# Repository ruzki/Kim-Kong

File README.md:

# Kim Kong
Daughterboard based on STM32F407VGT6 for the Speeduino ECU Project <br />
License <br />

<br />
This is a KiCad project of an Daughterboard to fit the kdFi by k-data.org (all rights reserved)  Motherboard Footprint.
Use most recent KiCad Nighty Build Version to open this project. 

This is not an k-data.org prouduct nor is it licencsed by k-data.org. 
You may contact k-data.org before using this Board on original k-data.org hardware and ask for permission.

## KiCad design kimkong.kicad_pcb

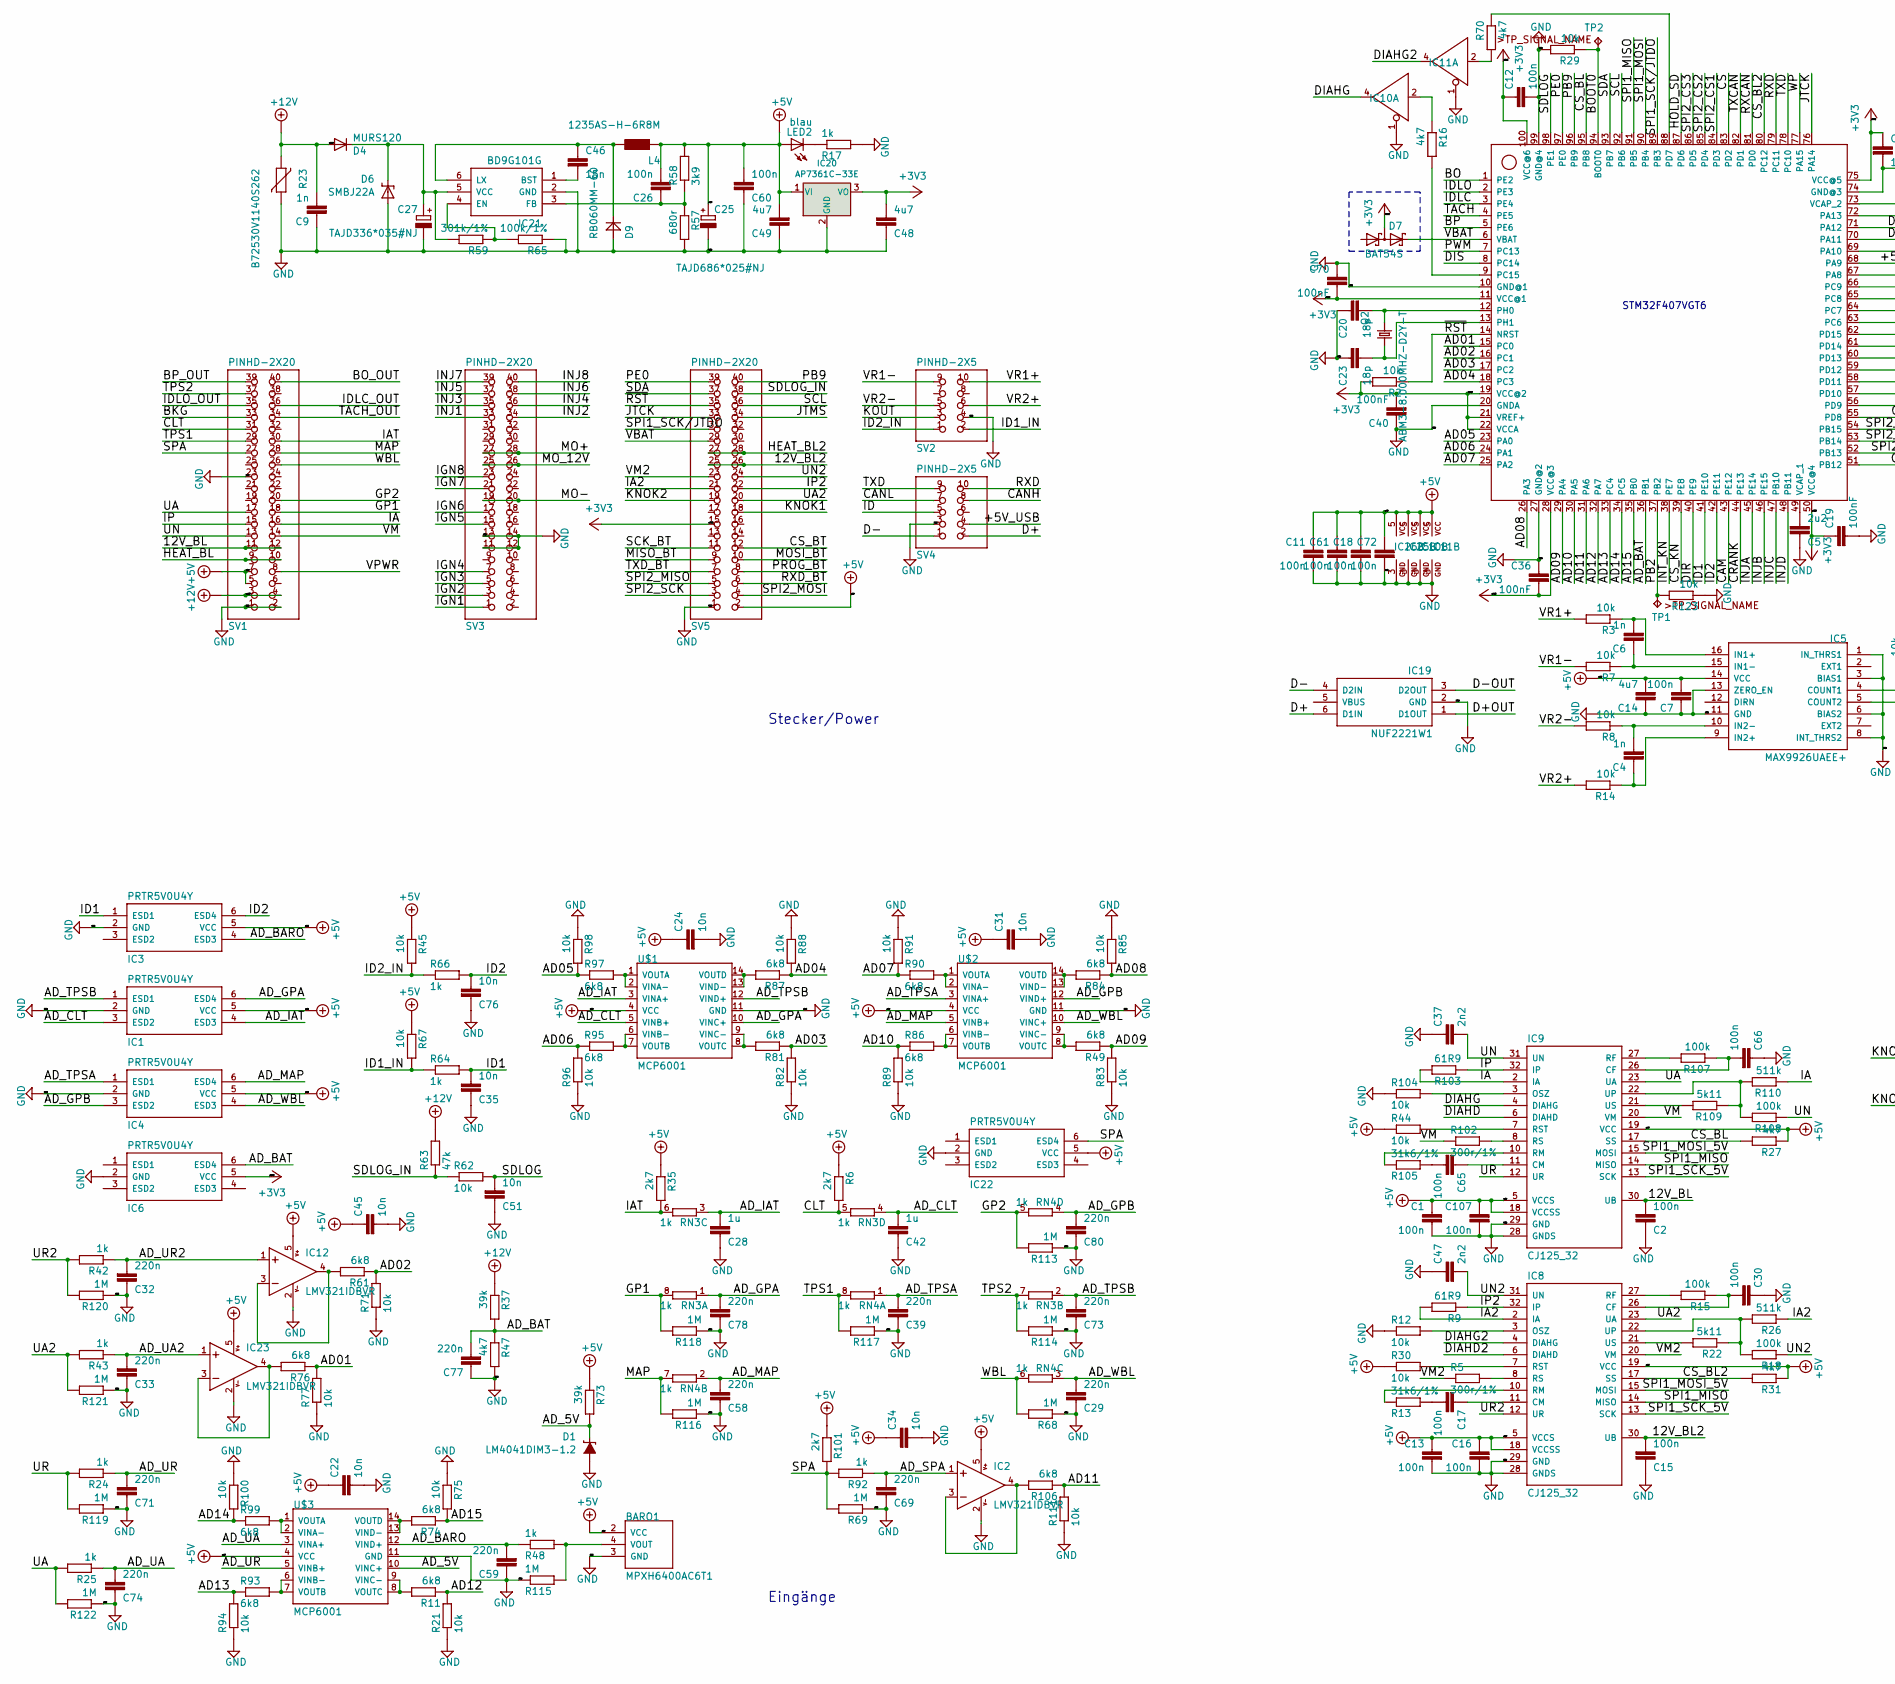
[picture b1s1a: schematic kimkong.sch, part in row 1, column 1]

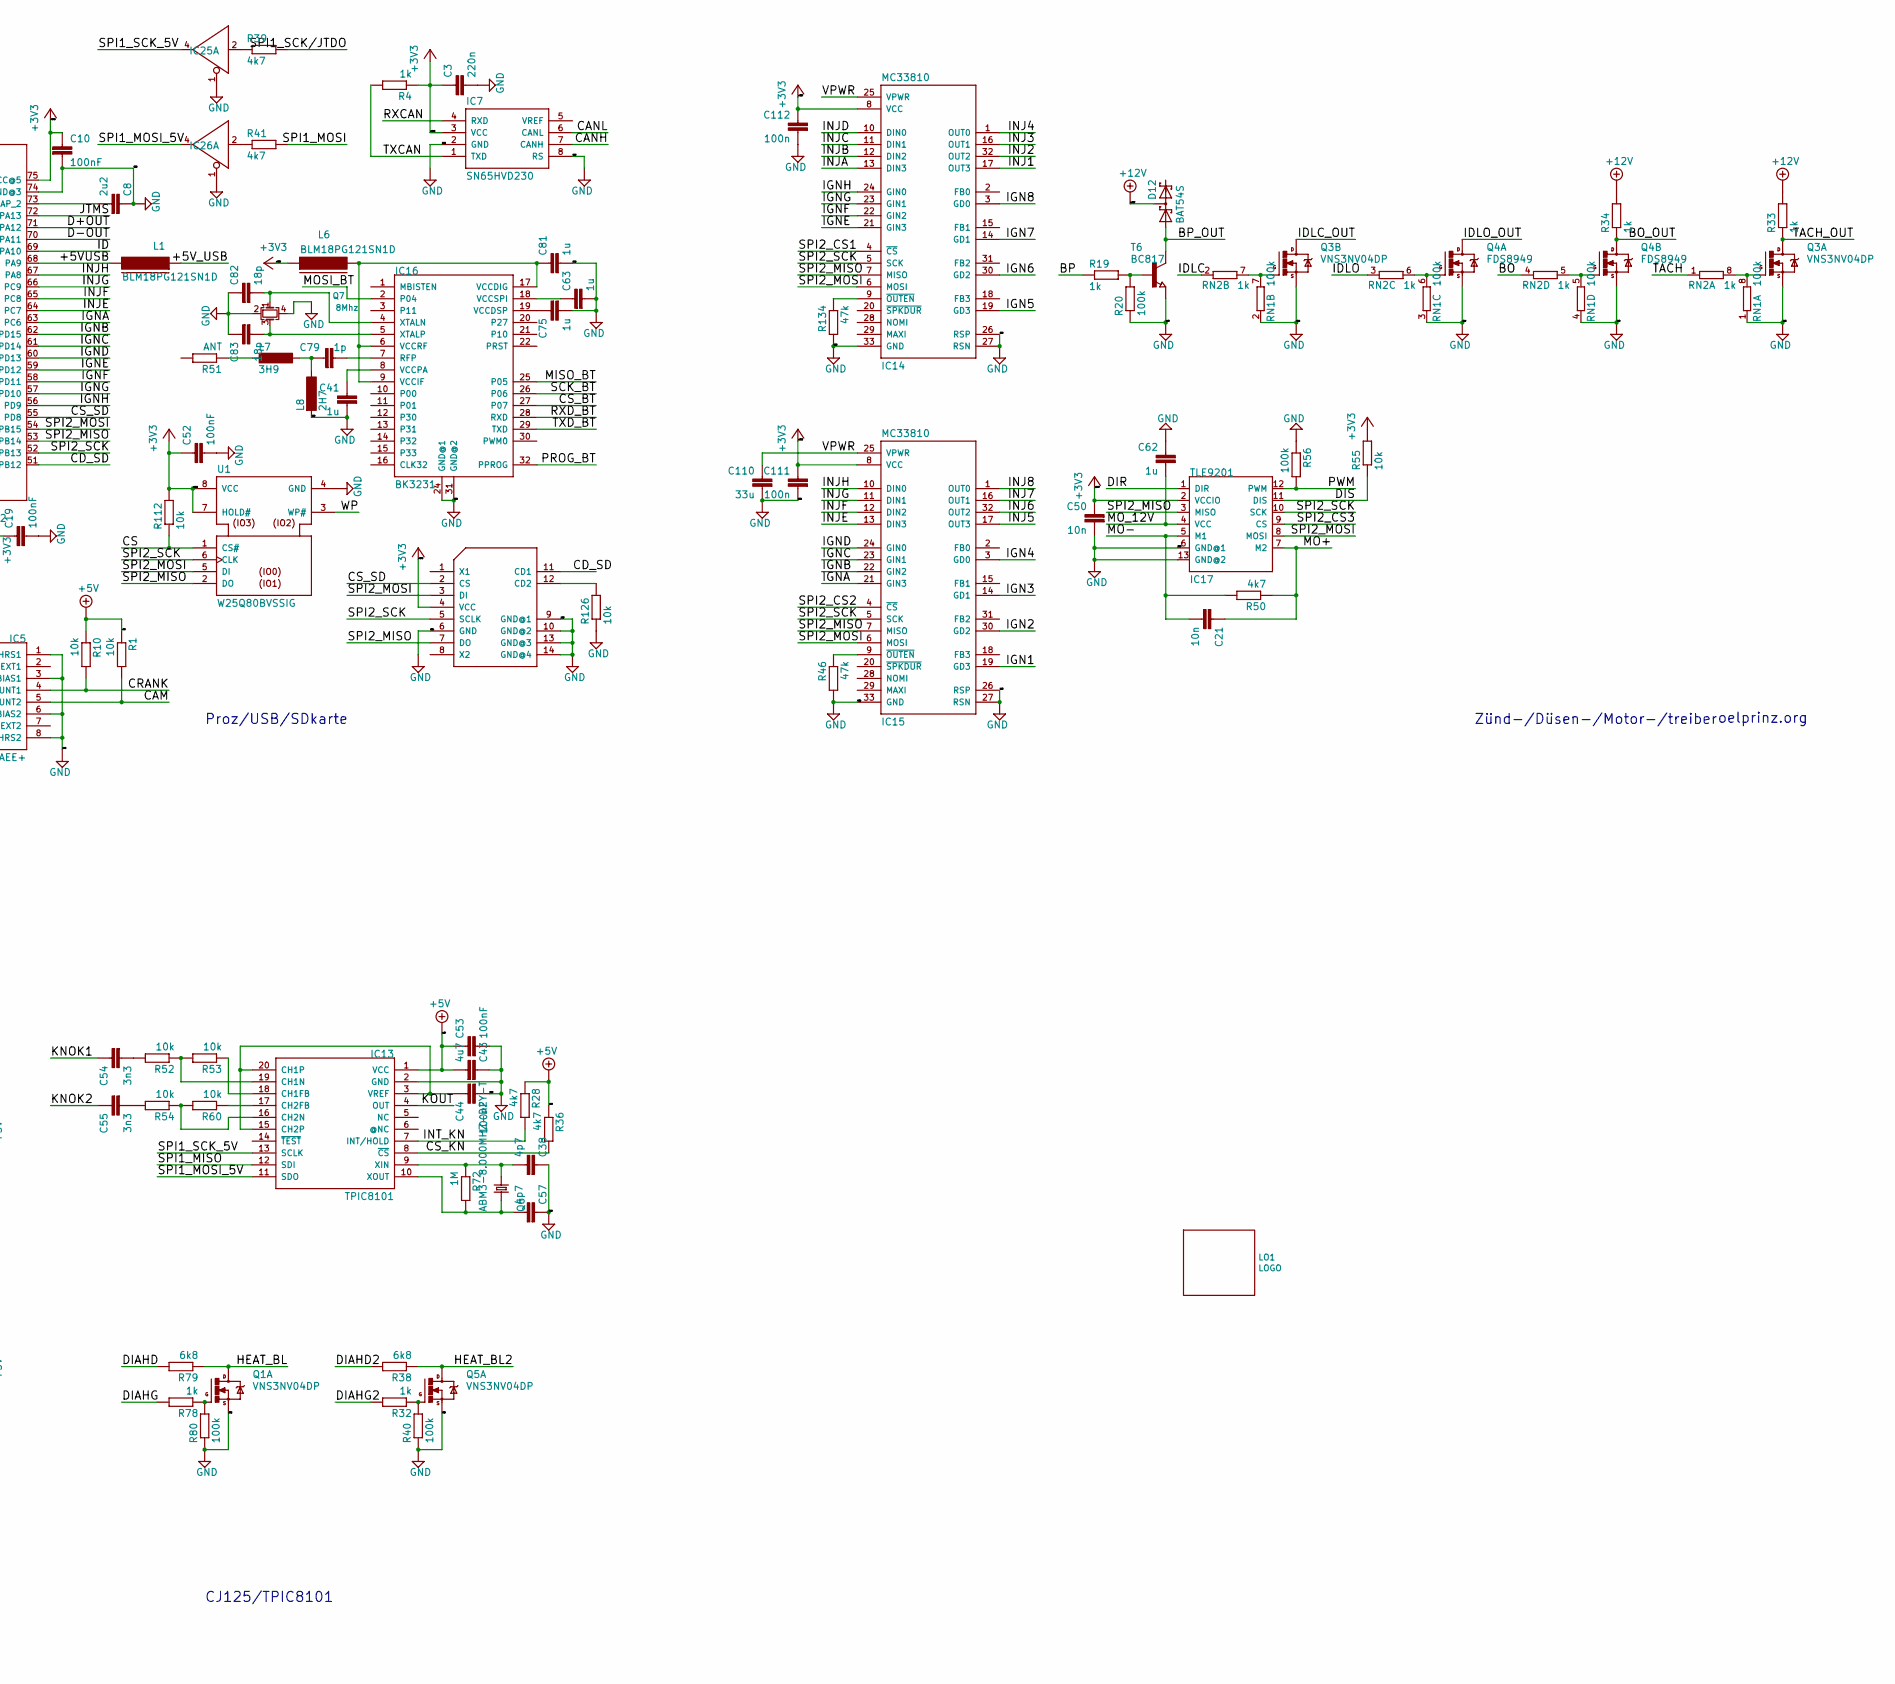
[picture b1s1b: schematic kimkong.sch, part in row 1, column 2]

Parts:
BARO1: MPXH6400AC6T1; Case1317
C1, C2, C7, C11, C12, C13, C15, C16, C17, C18, C26, C30, C60, C61, C65, C66, C72, C107, C111, C112: 100n; C0603
C3, C29, C32, C33, C39, C58, C59, C69, C71, C73, C74, C77, C78, C80: 220n; C0603
C4, C6: 1n; C0603
C5, C8: 2u2; C0603
C9: 1n; C0805
C10, C19, C36, C40, C44, C52, C53, C70: 100nF; C0603
C14, C48, C49: 4u7; C0603
C20, C23, C82, C83: 18p; C0603
C21: 10n; C1206
C22, C24, C31, C34, C35, C45, C50, C51, C76: 10n; C0603
C25: TAJD686*025#NJ; SMC_D
C27: TAJD336*035#NJ; SMC_D
C28, C41, C42, C62, C63, C75, C81: 1u; C0603
C37, C47: 2n2; C0603
C38, C57: 4p7; C0603
C43: 4u7; C0805
C46: 15n; C0603
C54, C55: 3n3; C0603
C79: 1p; C0603
C110: 33u; C1206
D1: LM4041DIM3-1.2; DBZ_R-PDSO-G3
D4: MURS120
D6: SMBJ22A; SMBJ
D7, D12: BAT54S; SOT23
D9: RB060MM-60
IC1, IC3, IC4, IC6, IC22: PRTR5V0U4Y; SOT363_PHILIPS
IC2, IC12, IC23: LMV321IDBVR; SC70-5L
IC5: MAX9926UAEE+; QSOP16
IC7: SN65HVD230; SO8
IC8, IC9: CJ125_32; TQFP32-08
IC10, IC11, IC25, IC26: 741G125DCK; SC70-5
IC13: TPIC8101; SO-20LD
IC14, IC15: MC33810
IC16: BK3231; QFN-32
IC17: TLE9201
IC18: STM32F407VGT6; LQFP100
IC19: NUF2221W1; SOT363_PHILIPS
IC20: AP7361C-33E; SOT-89-5_Housing
IC21: BD9G101G; SSOT6
L1, L6: BLM18PG121SN1D; FB805
L4: 1235AS-H-6R8M
L7: 3H9; L2012C
L8: 2H7; L2012C
LED2: blau; SML0805
LO1: LOGO; KimKong_40x50
Q1, Q3, Q5: VNS3NV04DP; M08A
Q2, Q6: ABM3-8.000MHZ-D2Y-T; ABM3
Q4: FDS8949; M08A
Q7: 8Mhz; ABM11
R1, R2, R10, R12, R21, R29, R30, R44, R45, R52, R53, R54, R55, R60, R62, R67, R71, R75, R77, R82, R83, R85, R88, R89, R91, R94, R96, R98, R100, R104, R111, R112, R123, R126: 10k; R0603
R3, R7, R8, R14: 10k; R1206
R4, R17, R19, R24, R25, R32, R33, R34, R42, R43, R48, R64, R66, R78, R92: 1k; R0603
R5, R102: 300r/1%; R0603
R6, R35, R101: 2k7; R0603
R9, R103: 61R9; R0603
R11, R38, R49, R61, R74, R76, R79, R81, R84, R86, R87, R90, R93, R95, R97, R99, R106: 6k8; R0603
R13, R105: 31k6/1%; R0603
R15, R18, R20, R40, R56, R80, R107, R108: 100k; R0603
R16, R27, R28, R31, R36, R39, R41, R47, R70: 4k7; R0603
R22, R109: 5k11; R0603
R23: B72530V1140S262; CT_CN1210
R26, R110: 511k; R0603
R37, R73: 39k; R0603
R46, R63, R134: 47k; R0603
R50: 4k7; R1206
R51: ANT; 2450AT18A100E
R57: 680r; R0603
R58: 3k9; R0603
R59: 301k/1%; R0603
R65: 100k/1%; R0603
R68, R69, R72, R113, R114, R115, R116, R117, R118, R119, R120, R121, R122: 1M; R0603
RN1: 100k; 0603-ARV
RN2, RN3, RN4: 1k; 0603-ARV
SV1, SV3, SV5: PINHD-2X20; 2X20
SV2, SV4: PINHD-2X5; 2X05
T6: BC817; SOT23
TP1, TP2: TPTP13R; TP13R
U1: W25Q80BVSSIG; SO08W
U$1, U$2, U$3: MCP6001; TSSOP14
U$6: AMPHENOL_1140084168

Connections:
+3V3: C3.1, C10.1, C12.1, C19.1, C36.2, C40.2, C48.2, C50.1, C52.1, C70.2, C111.1, C112.1, D7.3 (C1A2), IC6.5 (VCC), IC7.3 (VCC), IC14.8 (VCC), IC15.8 (VCC), IC17.2 (VCCIO), IC18.11 (VCC@1), IC18.19 (VCC@2), IC18.21 (VREF+), IC18.22 (VCCA), IC18.28 (VCC@3), IC18.50 (VCC@4), IC18.75 (VCC@5), IC18.100 (VCC@6), IC20.3 (VO), L6.2, R2.2, R4.1, R55.2, R112.2, SV5.15, U1.7 (HOLD#), U1.8 (VCC), U$6.4 (VCC)
+5V: BARO1.2 (VCC), C1.1, C7.2, C11.1, C13.1, C14.2, C16.1, C18.1, C22.1, C24.1, C25.+, C26.2, C31.1, C34.1, C43.2, C45.1, C49.2, C53.1, C60.2, C61.1, C72.1, C107.1, IC1.5 (VCC), IC2.5 (V+), IC3.5 (VCC), IC4.5 (VCC), IC5.14 (VCC), IC8.5 (VCCS), IC8.18 (VCCSS), IC8.19 (VCC), IC9.5 (VCCS), IC9.18 (VCCSS), IC9.19 (VCC), IC10.5 (VCC), IC11.5 (VCC), IC12.5 (V+), IC13.1 (VCC), IC20.1 (VI), IC22.5 (VCC), IC23.5 (V+), IC25.5 (VCC), IC26.5 (VCC), L4.1, LED2.A, R1.1, R6.1, R10.1, R27.1, R28.1, R30.1, R31.1, R35.1, R36.1, R44.1, R45.1, R58.2, R67.1, R73.1, R101.1, SV1.5, SV1.7, SV5.2, U$1.4 (VCC), U$2.4 (VCC), U$3.4 (VCC)
+12V: C9.2, D4.1 (A), D12.3 (C1A2), R23.2, R33.2, R34.2, R37.1, R63.2, SV1.3, SV1.4
/12V_BL: C2.2, IC9.30 (UB), SV1.11, SV1.12
/12V_BL2: C15.2, IC8.30 (UB), SV5.25, SV5.26
/+5VUSB: IC18.68 (PA9), L1.1
/+5V_USB: L1.2, SV4.4
/AD01: IC18.15 (PC0), R76.1, R77.2
/AD02: IC18.16 (PC1), R61.1, R71.2
/AD03: IC18.17 (PC2), R81.1, R82.2
/AD04: IC18.18 (PC3), R87.1, R88.2
/AD05: IC18.23 (PA0), R97.1, R98.2
/AD06: IC18.24 (PA1), R95.1, R96.2
/AD07: IC18.25 (PA2), R90.1, R91.2
/AD08: IC18.26 (PA3), R84.1, R85.2
/AD09: IC18.29 (PA4), R49.1, R83.2
/AD10: IC18.30 (PA5), R86.1, R89.2
/AD11: IC18.31 (PA6), R106.1, R111.2
/AD12: IC18.32 (PA7), R11.1, R21.2
/AD13: IC18.33 (PC4), R93.1, R94.2
/AD14: IC18.34 (PC5), R99.1, R100.2
/AD15: IC18.35 (PB0), R74.1, R75.2
/AD_5V: D1.1 (C), R73.2, U$3.10 (VINC+)
/AD_BARO: C59.2, IC3.4 (ESD3), R48.1, U$3.12 (VIND+)
/AD_BAT: C77.2, IC6.6 (ESD4), IC18.36 (PB1), R37.2, R47.1
/AD_CLT: C42.2, IC1.3 (ESD2), RN3.4 (1), U$1.5 (VINB+)
/AD_GPA: C78.2, IC1.6 (ESD4), RN3.1, U$1.10 (VINC+)
/AD_GPB: C80.2, IC4.3 (ESD2), RN4.4 (1), U$2.12 (VIND+)
/AD_IAT: C28.2, IC1.4 (ESD3), RN3.3 (1), U$1.3 (VINA+)
/AD_MAP: C58.2, IC4.6 (ESD4), RN4.2 (1), U$2.5 (VINB+)
/AD_SPA: C69.2, IC2.1 (+IN), R92.1
/AD_TPSA: C39.2, IC4.1 (ESD1), RN4.1, U$2.3 (VINA+)
/AD_TPSB: C73.2, IC1.1 (ESD1), RN3.2 (1), U$1.12 (VIND+)
/AD_UA: C74.2, R25.1, U$3.3 (VINA+)
/AD_UA2: C33.2, IC23.1 (+IN), R43.1
/AD_UR: C71.2, R24.1, U$3.5 (VINB+)
/AD_UR2: C32.2, IC12.1 (+IN), R42.1
/AD_WBL: C29.2, IC4.4 (ESD3), RN4.3 (1), U$2.10 (VINC+)
/BKG: SV1.33
/BO: IC18.1 (PE2), RN2.4 (1)
/BOOT0: IC18.94 (BOOT0), R29.1, TP2.TP
/BO_OUT: Q4.5 (D), Q4.6 (D), R34.1, SV1.40
/BP: IC18.5 (PE6), R19.1
/BP_OUT: D12.1 (A1), SV1.39, T6.3 (C)
/CAM: IC5.5 (COUNT2), IC18.43 (PE12), R1.2
/CANH: IC7.7 (CANH), SV4.8
/CANL: IC7.6 (CANL), SV4.7
/CD_SD: IC18.51 (PB12), U$6.11 (CD1)
/CLT: R6.2, RN3.5 (2), SV1.31
/CRANK: IC5.4 (COUNT1), IC18.44 (PE13), R10.2
/CS: IC18.83 (PD2), R112.1, U1.1 (CS#)
/CS_BL: IC9.17 (SS), IC18.95 (PB8), R27.2
/CS_BL2: IC8.17 (SS), IC18.80 (PC12), R31.2
/CS_BT: IC16.27 (P07), SV5.12
/CS_KN: IC13.8 (~CS), IC18.39 (PE8), R36.2
/CS_SD: IC18.55 (PD8), U$6.2 (CS)
/D+: IC19.6 (D1IN), SV4.2
/D+OUT: IC18.71 (PA12), IC19.1 (D1OUT)
/D-: IC19.4 (D2IN), SV4.1
/D-OUT: IC18.70 (PA11), IC19.3 (D2OUT)
/DIAHD: IC9.6 (DIAHD), R79.2
/DIAHD2: IC8.6 (DIAHD), R38.2
/DIAHG: IC9.4 (DIAHG), IC10.4 (O), R78.2
/DIAHG2: IC8.4 (DIAHG), IC11.4 (O), R32.2
/DIR: IC17.1 (DIR), IC18.40 (PE9)
/DIS: IC17.11 (DIS), IC18.8 (PC14), R55.1
/GP1: R118.2, RN3.8 (2), SV1.18
/GP2: R113.2, RN4.5 (2), SV1.20
/HEAT_BL: Q1.7 (D), Q1.8 (D), R79.1, SV1.9, SV1.10
/HEAT_BL2: Q5.7 (D), Q5.8 (D), R38.1, SV5.27, SV5.28
/HOLD_SD: IC18.87 (PD6)
/IA: IC9.2 (IA), R103.2, R110.1, SV1.16
/IA2: IC8.2 (IA), R9.2, R26.1, SV5.21
/IAT: R35.2, RN3.6 (2), SV1.30
/ID: IC18.69 (PA10), SV4.5
/ID1: C35.2, IC3.1 (ESD1), IC18.41 (PE10), R64.2
/ID1_IN: R64.1, R67.2, SV2.2
/ID2: C76.2, IC3.6 (ESD4), IC18.42 (PE11), R66.2
/ID2_IN: R45.2, R66.1, SV2.1
/IDLC: IC18.3 (PE4), RN2.2 (1)
/IDLC_OUT: Q3.5 (D), Q3.6 (D), SV1.36
/IDLO: IC18.2 (PE3), RN2.3 (1)
/IDLO_OUT: Q4.7 (D), Q4.8 (D), SV1.35
/IGN1: IC15.19 (GD3), SV3.1
/IGN2: IC15.30 (GD2), SV3.3
/IGN3: IC15.14 (GD1), SV3.5
/IGN4: IC15.3 (GD0), SV3.7
/IGN5: IC14.19 (GD3), SV3.15
/IGN6: IC14.30 (GD2), SV3.17
/IGN7: IC14.14 (GD1), SV3.21
/IGN8: IC14.3 (GD0), SV3.23
/IGNA: IC15.21 (GIN3), IC18.63 (PC6)
/IGNB: IC15.22 (GIN2), IC18.62 (PD15)
/IGNC: IC15.23 (GIN1), IC18.61 (PD14)
/IGND: IC15.24 (GIN0), IC18.60 (PD13)
/IGNE: IC14.21 (GIN3), IC18.59 (PD12)
/IGNF: IC14.22 (GIN2), IC18.58 (PD11)
/IGNG: IC14.23 (GIN1), IC18.57 (PD10)
/IGNH: IC14.24 (GIN0), IC18.56 (PD9)
/INJ1: IC14.17 (OUT3), SV3.33
/INJ2: IC14.32 (OUT2), SV3.34
/INJ3: IC14.16 (OUT1), SV3.35
/INJ4: IC14.1 (OUT0), SV3.36
/INJ5: IC15.17 (OUT3), SV3.37
/INJ6: IC15.32 (OUT2), SV3.38
/INJ7: IC15.16 (OUT1), SV3.39
/INJ8: IC15.1 (OUT0), SV3.40
/INJA: IC14.13 (DIN3), IC18.45 (PE14)
/INJB: IC14.12 (DIN2), IC18.46 (PE15)
/INJC: IC14.11 (DIN1), IC18.47 (PB10)
/INJD: IC14.10 (DIN0), IC18.48 (PB11)
/INJE: IC15.13 (DIN3), IC18.64 (PC7)
/INJF: IC15.12 (DIN2), IC18.65 (PC8)
/INJG: IC15.11 (DIN1), IC18.66 (PC9)
/INJH: IC15.10 (DIN0), IC18.67 (PA8)
/INT_KN: IC13.7 (INT/HOLD), IC18.38 (PE7), R28.2
/IP: IC9.32 (IP), R103.1, SV1.15
/IP2: IC8.32 (IP), R9.1, SV5.22
/JTCK: IC18.76 (PA14), SV5.33
/JTMS: IC18.72 (PA13), SV5.34
/KNOK1: C54.1, SV5.18
/KNOK2: C55.1, SV5.19
/KOUT: IC13.4 (OUT), SV2.3
/MAP: R116.2, RN4.7 (2), SV1.28
/MISO_BT: IC16.25 (P05), SV5.9
/MO+: C21.1, IC17.7 (M2), R50.1, SV3.27, SV3.28
/MO-: C21.2, IC17.5 (M1), R50.2, SV3.19, SV3.20
/MOSI_BT: IC16.2 (P04), SV5.10
/MO_12V: C62.2, IC17.4 (VCC), SV3.25, SV3.26
/PB2: IC18.37 (PB2), R123.2, TP1.TP
/PB9: IC18.96 (PB9), SV5.40
/PE0: IC18.97 (PE0), SV5.39
/PROG_BT: IC16.32 (PPROG), SV5.8
/PWM: IC17.12 (PWM), IC18.7 (PC13), R56.2
/RXCAN: IC7.4 (RXD), IC18.81 (PD0)
/RXD: IC18.79 (PC11), SV4.10
/RXD_BT: IC16.28 (RXD), SV5.6
/SCK_BT: IC16.26 (P06), SV5.11
/SCL: IC18.92 (PB6), SV5.36
/SDA: IC18.93 (PB7), SV5.37
/SDLOG: C51.2, IC18.98 (PE1), R62.2
/SDLOG_IN: R62.1, R63.1, SV5.38
/SPA: IC22.6 (ESD4), R69.2, R92.2, R101.2, SV1.27
/SPI1_MISO: IC8.14 (MISO), IC9.14 (MISO), IC13.12 (SDI), IC18.91 (PB5)
/SPI1_MOSI: IC18.90 (PB4), R41.2
/SPI1_MOSI_5V: IC8.15 (MOSI), IC9.15 (MOSI), IC13.11 (SDO), IC26.4 (O)
/SPI1_SCK/JTDO: IC18.89 (PB3), R39.2, SV5.31
/SPI1_SCK_5V: IC8.13 (SCK), IC9.13 (SCK), IC13.13 (SCLK), IC25.4 (O)
/SPI2_CS1: IC14.4 (~CS), IC18.84 (PD3)
/SPI2_CS2: IC15.4 (~CS), IC18.85 (PD4)
/SPI2_CS3: IC17.9 (CS), IC18.86 (PD5)
/SPI2_MISO: IC14.7 (MISO), IC15.7 (MISO), IC17.3 (MISO), IC18.53 (PB14), SV5.5, U1.2 (DO), U$6.7 (DO)
/SPI2_MOSI: IC14.6 (MOSI), IC15.6 (MOSI), IC17.8 (MOSI), IC18.54 (PB15), SV5.4, U1.5 (DI), U$6.3 (DI)
/SPI2_SCK: IC14.5 (SCK), IC15.5 (SCK), IC17.10 (SCK), IC18.52 (PB13), SV5.3, U1.6 (CLK), U$6.5 (SCLK)
/TACH: IC18.4 (PE5), RN2.1
/TACH_OUT: Q3.7 (D), Q3.8 (D), R33.1, SV1.34
/TPS1: R117.2, RN4.8 (2), SV1.29
/TPS2: R114.2, RN3.7 (2), SV1.37
/TXCAN: IC7.1 (TXD), IC18.82 (PD1), R4.2
/TXD: IC18.78 (PC10), SV4.9
/TXD_BT: IC16.29 (TXD), SV5.7
/UA: IC9.23 (UA), R25.2, R122.2, SV1.17
/UA2: IC8.23 (UA), R43.2, R121.2, SV5.20
/UN: C37.2, IC9.31 (UN), R108.1, SV1.13
/UN2: C47.2, IC8.31 (UN), R18.1, SV5.24
/UR: IC9.12 (UR), R24.2, R119.2
/UR2: IC8.12 (UR), R42.2, R120.2
/VBAT: D7.2 (C2), IC18.6 (VBAT), SV5.29
/VM: IC9.20 (VM), R102.1, SV1.14
/VM2: IC8.20 (VM), R5.1, SV5.23
/VPWR: C110.1, IC14.25 (VPWR), IC15.25 (VPWR), SV1.8
/VR1+: R3.2, SV2.10
/VR1-: R7.2, SV2.9
/VR2+: R14.2, SV2.6
/VR2-: R8.2, SV2.5
/WBL: R68.2, RN4.6 (2), SV1.26
/WP: IC18.77 (PA15), U1.3 (WP#)
/~RST: IC18.14 (NRST), R2.1, SV5.35
GND: BARO1.3 (GND), C1.2, C2.1, C3.2, C5.1, C7.1, C8.1, C9.1, C10.2, C11.2, C12.2, C13.2, C14.1, C15.1, C16.2, C18.2, C19.2, C20.1, C22.2, C23.1, C24.2, C25.-, C27.-, C28.1, C29.1, C30.1, C31.2, C32.1, C33.1, C34.2, C35.1, C36.1, C37.1, C38.1, C39.1, C40.1, C41.2, C42.1, C43.1, C44.2, C45.2, C47.1, C48.1, C49.1, C50.2, C51.1, C52.2, C53.2, C57.1, C58.1, C59.1, C60.1, C61.2, C62.1, C63.2, C66.1, C69.1, C70.1, C71.1, C72.2, C73.1, C74.1, C75.2, C76.1, C77.1, C78.1, C80.1, C81.2, C82.1, C83.1, C107.2, C110.2, C111.2, C112.2, D1.2 (A), D6.A, D9.1, IC1.2 (GND), IC2.2 (V-), IC3.2 (GND), IC4.2 (GND), IC5.1 (IN_THRS1), IC5.3 (BIAS1), IC5.6 (BIAS2), IC5.8 (INT_THRS2), IC5.11 (GND), IC5.13 (ZERO_EN), IC6.2 (GND), IC7.2 (GND), IC7.8 (RS), IC8.28 (GNDS), IC8.29 (GND), IC9.28 (GNDS), IC9.29 (GND), IC10.1 (OE), IC10.3 (GND), IC11.1 (OE), IC11.3 (GND), IC12.2 (V-), IC13.2 (GND), IC14.26 (RSP), IC14.27 (RSN), IC14.33 (GND), IC15.26 (RSP), IC15.27 (RSN), IC15.33 (GND), IC16.24 (GND@1), IC16.31 (GND@2), IC17.6 (GND@1), IC17.13 (GND@2), IC18.10 (GND@1), IC18.20 (GNDA), IC18.27 (GND@2), IC18.74 (GND@3), IC18.99 (GND@4), IC19.2 (GND), IC20.2 (GND), IC21.2 (GND), IC22.2 (GND), IC23.2 (V-), IC25.1 (OE), IC25.3 (GND), IC26.1 (OE), IC26.3 (GND), L8.2, Q1.1 (S), Q3.1 (S), Q3.3 (S), Q4.1 (S), Q4.3 (S), Q5.1 (S), Q7.2, Q7.4, R12.1, R17.2, R20.1, R21.1, R23.1, R29.2, R40.1, R46.2, R47.2, R56.1, R57.2, R65.1, R68.1, R69.1, R71.1, R75.1, R77.1, R80.1, R82.1, R83.1, R85.1, R88.1, R89.1, R91.1, R94.1, R96.1, R98.1, R100.1, R104.1, R111.1, R113.1, R114.1, R115.1, R116.1, R117.1, R118.1, R119.1, R120.1, R121.1, R122.1, R123.1, R126.1, R134.2, RN1.1, RN1.2 (1), RN1.3 (1), RN1.4 (1), SV1.1, SV1.2, SV1.23, SV2.4, SV3.11, SV3.12, SV3.13, SV3.14, SV4.3, SV5.1, T6.2 (E), U1.4 (GND), U$1.11 (GND), U$2.11 (GND), U$3.11 (GND), U$6.6 (GND), U$6.9 (GND@1), U$6.10 (GND@2), U$6.13 (GND@3), U$6.14 (GND@4)
unnamed: BARO1.4 (VOUT), R48.2, R115.2
unnamed: C4.1, IC5.9 (IN2+), R14.1
unnamed: C4.2, IC5.10 (IN2-), R8.1
unnamed: C5.2, IC18.49 (VCAP_1)
unnamed: C6.1, IC5.15 (IN1-), R7.1
unnamed: C6.2, IC5.16 (IN1+), R3.1
unnamed: C8.2, IC18.73 (VCAP_2)
unnamed: C17.1, IC8.11 (CM)
unnamed: C17.2, R13.2
unnamed: C20.2, IC18.12 (PH0), Q2.1
unnamed: C23.2, IC18.13 (PH1), Q2.2
unnamed: C26.1, IC21.3 (FB), R57.1, R58.1
unnamed: C27.+, D4.2 (C), D6.C, IC21.5 (VCC), R59.2
unnamed: C30.2, IC8.26 (CF), R15.1
unnamed: C38.2, IC13.9 (XIN), Q6.2, R72.1
unnamed: C41.1, IC16.8 (VCCPA)
unnamed: C44.1, IC13.3 (VREF), IC13.15 (CH2P), IC13.20 (CH1P)
unnamed: C46.1, D9.2, IC21.6 (LX), L4.2
unnamed: C46.2, IC21.1 (BST)
unnamed: C54.2, R52.2
unnamed: C55.2, R54.2
unnamed: C57.2, IC13.10 (XOUT), Q6.1, R72.2
unnamed: C63.1, IC16.18 (VCCSPI)
unnamed: C65.1, IC9.11 (CM)
unnamed: C65.2, R105.2
unnamed: C66.2, IC9.26 (CF), R107.1
unnamed: C75.1, IC16.19 (VCCDSP)
unnamed: C79.1, L7.1, L8.1
unnamed: C79.2, IC16.7 (RFP)
unnamed: C81.1, IC16.6 (VCCRF), IC16.9 (VCCIF), IC16.17 (VCCDIG), L6.1
unnamed: C82.2, IC16.4 (XTALN), Q7.1
unnamed: C83.2, IC16.5 (XTALP), Q7.3
unnamed: IC2.3 (-IN), IC2.4 (OUT), R106.2
unnamed: IC8.3 (OSZ), R12.2
unnamed: IC8.7 (RST), R30.2
unnamed: IC8.8 (RS), R5.2
unnamed: IC8.10 (RM), R13.1
unnamed: IC8.21 (US), R22.2
unnamed: IC8.22 (UP), R18.2, R22.1, R26.2
unnamed: IC8.27 (RF), R15.2
unnamed: IC9.3 (OSZ), R104.2
unnamed: IC9.7 (RST), R44.2
unnamed: IC9.8 (RS), R102.2
unnamed: IC9.10 (RM), R105.1
unnamed: IC9.21 (US), R109.2
unnamed: IC9.22 (UP), R108.2, R109.1, R110.2
unnamed: IC9.27 (RF), R107.2
unnamed: IC10.2 (I), R16.1
unnamed: IC11.2 (I), R70.2
unnamed: IC12.3 (-IN), IC12.4 (OUT), R61.2
unnamed: IC13.16 (CH2N), R54.1, R60.2
unnamed: IC13.17 (CH2FB), R60.1
unnamed: IC13.18 (CH1FB), R53.1
unnamed: IC13.19 (CH1N), R52.1, R53.2
unnamed: IC14.9 (~OUTEN), R134.1
unnamed: IC15.9 (~OUTEN), R46.1
unnamed: IC18.9 (PC15), R16.2
unnamed: IC18.88 (PD7), R70.1
unnamed: IC21.4 (EN), R59.1, R65.2
unnamed: IC23.3 (-IN), IC23.4 (OUT), R76.2
unnamed: IC25.2 (I), R39.1
unnamed: IC26.2 (I), R41.1
unnamed: L7.2, R51.1
unnamed: LED2.C, R17.1
unnamed: Q1.2 (G), R78.1, R80.2
unnamed: Q3.2 (G), RN1.8 (2), RN2.8 (2)
unnamed: Q3.4 (G), RN1.7 (2), RN2.7 (2)
unnamed: Q4.2 (G), RN1.6 (2), RN2.6 (2)
unnamed: Q4.4 (G), RN1.5 (2), RN2.5 (2)
unnamed: Q5.2 (G), R32.1, R40.2
unnamed: R11.2, U$3.8 (VOUTC), U$3.9 (VINC-)
unnamed: R19.2, R20.2, T6.1 (B)
unnamed: R49.2, U$2.8 (VOUTC), U$2.9 (VINC-)
unnamed: R74.2, U$3.13 (VIND-), U$3.14 (VOUTD)
unnamed: R81.2, U$1.8 (VOUTC), U$1.9 (VINC-)
unnamed: R84.2, U$2.13 (VIND-), U$2.14 (VOUTD)
unnamed: R86.2, U$2.6 (VINB-), U$2.7 (VOUTB)
unnamed: R87.2, U$1.13 (VIND-), U$1.14 (VOUTD)
unnamed: R90.2, U$2.1 (VOUTA), U$2.2 (VINA-)
unnamed: R93.2, U$3.6 (VINB-), U$3.7 (VOUTB)
unnamed: R95.2, U$1.6 (VINB-), U$1.7 (VOUTB)
unnamed: R97.2, U$1.1 (VOUTA), U$1.2 (VINA-)
unnamed: R99.2, U$3.1 (VOUTA), U$3.2 (VINA-)
unnamed: R126.2, U$6.12 (CD2)

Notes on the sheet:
Stecker/Power
Eingänge
CJ125/TPIC8101
Proz/USB/SDkarte
STM32F407VGT6
Zünd-/Düsen-/Motor-/treiber
oelprinz.org

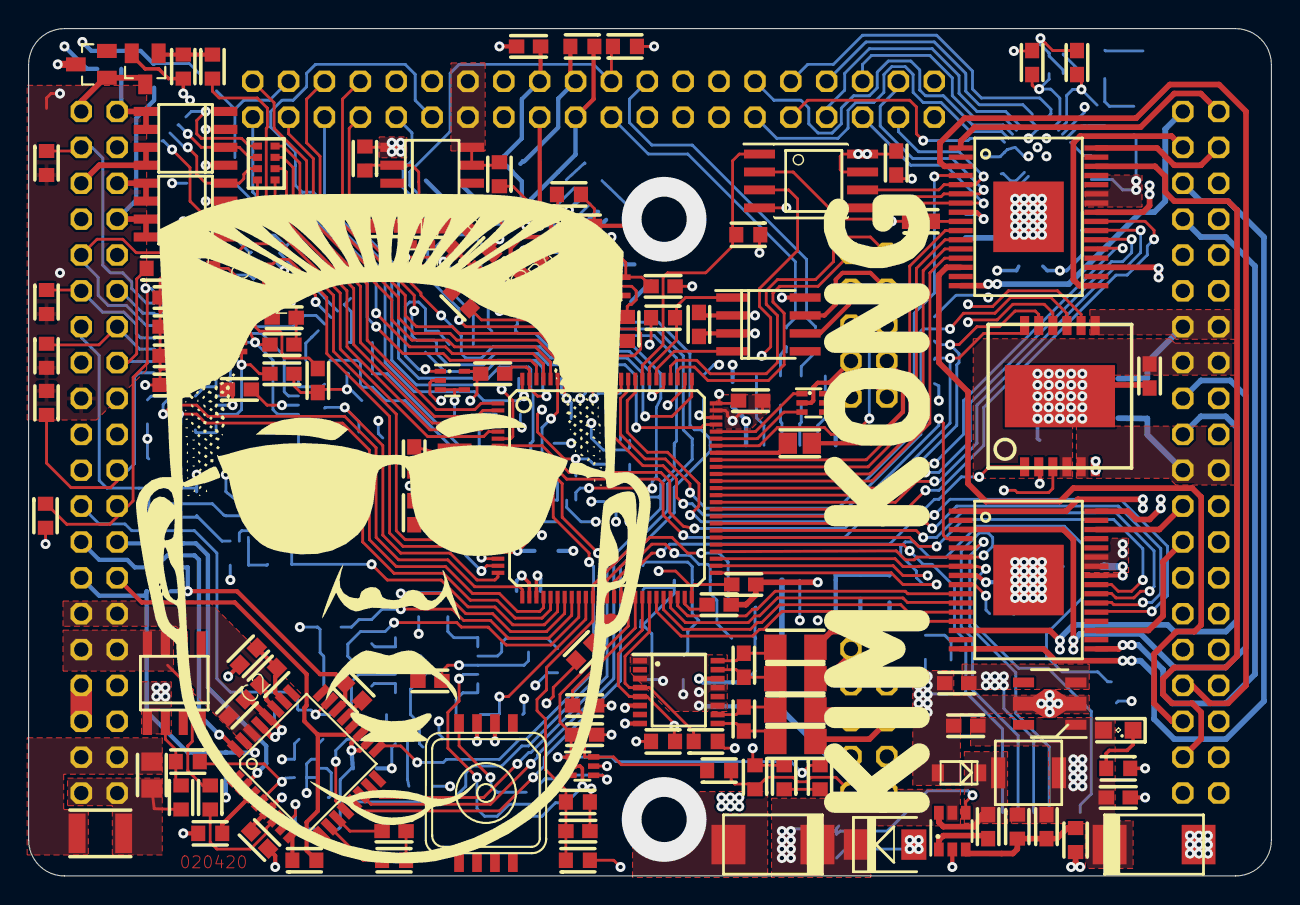
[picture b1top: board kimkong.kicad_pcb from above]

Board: 4 copper layers, 88.0 x 60.0 mm, 271 parts (0 on the bottom side), 261 nets.

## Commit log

2020-04-10 1st upload
2020-04-10 Remove some files

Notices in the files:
README.md:
License: CC BY-NC 4.0
